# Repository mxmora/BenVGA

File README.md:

# BenVGA
Ben's VGA card in PCB form

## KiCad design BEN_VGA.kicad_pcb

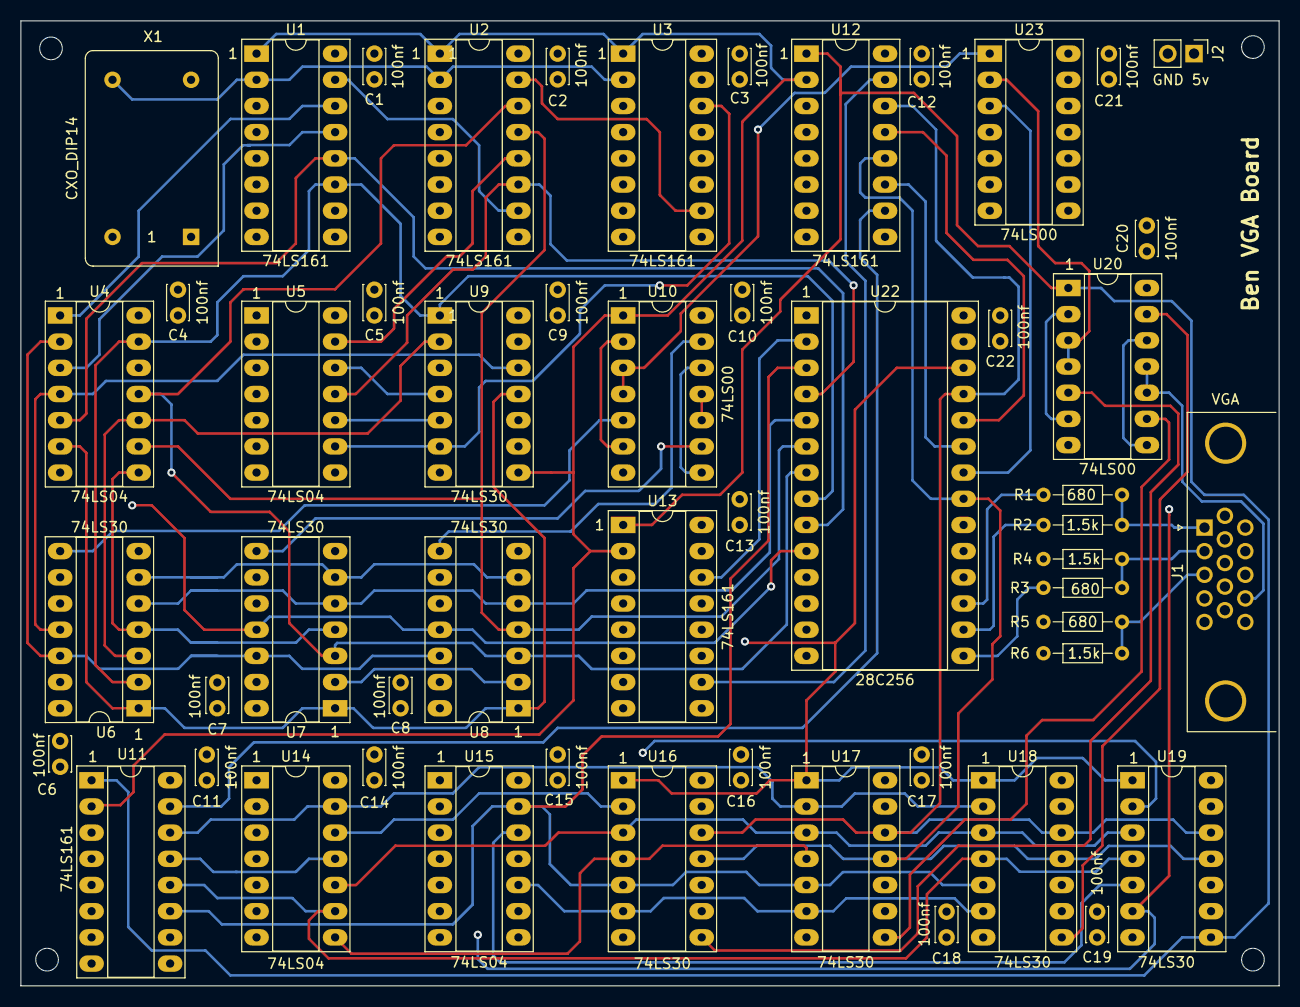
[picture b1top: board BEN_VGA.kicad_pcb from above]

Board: 4 copper layers, 122.0 x 93.6 mm, 57 parts (0 on the bottom side), 65 nets.

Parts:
C1, C2, C3, C4, C5, C6, C7, C8, C9, C10, C11, C12, C13, C14, C15, C16, C17, C18, C19, C20, C21, C22: 100nf; C_Disc_D3.4mm_W2.1mm_P2.50mm
H1, H2, H3, H4: MountingHole; MountingHole_2.2mm_M2
J1: VGA; DSUB-15-HD_Female_Horizontal_P2.29x1.98mm_EdgePinOffset3.03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
J2: GND 5v; PinHeader_1x02_P2.54mm_Vertical
R1, R3, R5: 680; R_Axial_DIN0204_L3.6mm_D1.6mm_P7.62mm_Horizontal
R2, R4, R6: 1.5k; R_Axial_DIN0204_L3.6mm_D1.6mm_P7.62mm_Horizontal
U1, U2, U3, U11, U12, U13: 74LS161; DIP-16_W7.62mm_Socket_LongPads
U4, U5, U14, U15: 74LS04; DIP-14_W7.62mm_Socket_LongPads
U6, U7, U8, U9, U16, U17, U18, U19: 74LS30; DIP-14_W7.62mm_Socket_LongPads
U10, U20, U23: 74LS00; DIP-14_W7.62mm_Socket_LongPads
U22: 28C256; DIP-28_W15.24mm_Socket_LongPads
X1: CXO_DIP14; Oscillator_DIP-14

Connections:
+5V: C1.1, C2.1, C3.1, C4.1, C5.1, C6.1, C7.1, C8.1, C9.1, C10.1, C11.1, C12.1, C13.1, C14.1, C15.1, C16.1, C17.1, C18.1, C19.1, C20.1, C21.1, C22.1, J2.1, U1.7, U1.9, U1.10, U1.16, U2.7, U2.9, U2.16, U3.7, U3.9, U3.16, U4.14, U5.14, U6.14, U7.14, U8.14, U9.14, U10.14, U11.7, U11.9, U11.10, U11.16, U12.7, U12.9, U12.16, U13.7, U13.9, U13.16, U14.14, U15.14, U16.14, U17.14, U18.7, U19.7, U20.14, U22.27, U22.28, U23.14, X1.1, X1.14
/HSync/264: U1.1, U2.1, U3.1, U9.8, U10.1, U11.2, U12.2, U13.2
/HSync/CLK: U1.2, U2.2, U3.2, X1.8
/HSync/HBLANK: U10.3, U10.4, U23.1
/HSync/Q0: U1.14, U4.1
/HSync/Q1: U1.13, U4.3, U7.11, U8.11, U22.10
/HSync/Q2: U1.12, U4.5, U22.9
/HSync/Q3: U1.11, U4.13, U6.2, U9.1, U22.8
/HSync/Q4: U2.14, U4.11, U7.3, U8.3, U22.7
/HSync/Q5: U2.13, U4.9, U8.4, U22.6
/HSync/Q6: U2.12, U5.13, U6.5, U7.5, U8.5, U22.5
/HSync/Q7: U2.11, U5.11, U6.6, U7.6, U8.6, U22.4
/HSync/Q8: U3.14, U5.9, U9.6
/VSync/Q0: U11.14, U14.13, U17.2, U18.2
/VSync/Q1: U11.13, U14.11
/VSync/Q2: U11.12, U14.9, U18.4, U19.4
/VSync/Q3: U11.11, U15.13, U16.5, U17.5, U18.5, U22.3
/VSync/Q4: U12.14, U16.12, U17.12, U18.12, U19.12, U22.25
/VSync/Q5: U12.13, U15.11, U19.6, U22.24
/VSync/Q6: U12.12, U16.11, U17.11, U18.11, U19.11, U22.21
/VSync/Q7: U12.11, U22.23
/VSync/Q8: U13.14, U22.2
/VSync/Q9: U13.13, U16.1, U17.1, U18.1, U19.1, U22.26
/VSync/VBLANK: U20.3, U20.4, U23.2
GND: C1.2, C2.2, C3.2, C4.2, C5.2, C6.2, C7.2, C8.2, C9.2, C10.2, C11.2, C12.2, C13.2, C14.2, C15.2, C16.2, C17.2, C18.2, C19.2, C20.2, C21.2, C22.2, J1.5, J1.6, J1.7, J1.8, J1.10, J2.2, U1.8, U2.8, U3.8, U4.7, U5.7, U6.7, U7.7, U8.7, U9.7, U10.7, U11.8, U12.8, U13.8, U14.7, U15.7, U16.7, U17.7, U18.14, U19.14, U20.7, U22.1, U22.14, U22.20, U23.7, X1.7
HSYNC: J1.13, U10.10, U10.11
unnamed: J1.1, R1.2, R2.2
unnamed: J1.2, R3.2, R4.2
unnamed: J1.3, R5.2, R6.2
unnamed: R1.1, U22.17
unnamed: R2.1, U22.16
unnamed: R3.1, U22.15
unnamed: R4.1, U22.13
unnamed: R5.1, U22.12
unnamed: R6.1, U22.11
unnamed: U1.15, U2.10
unnamed: U2.15, U3.10
unnamed: U4.2, U6.12, U7.12, U8.12
unnamed: U4.4, U6.11, U9.12
unnamed: U4.6, U6.1, U7.1, U8.1, U9.11
unnamed: U4.8, U6.4, U7.4, U9.3
unnamed: U4.10, U6.3, U9.2
unnamed: U4.12, U7.2, U8.2
unnamed: U5.10, U9.5
unnamed: U5.12, U9.4
unnamed: U10.2, U10.6
unnamed: U6.8, U10.5
unnamed: U7.8, U10.9
unnamed: U10.8, U10.12
unnamed: U8.8, U10.13
unnamed: U11.1, U12.1, U13.1, U19.8, U20.1
unnamed: U11.15, U12.10
unnamed: U12.15, U13.10
unnamed: U14.8, U16.4, U17.4
unnamed: U14.10, U16.3, U17.3, U18.3, U19.3
unnamed: U14.12, U16.2, U19.2
unnamed: U15.10, U16.6, U17.6, U18.6
unnamed: U15.12, U19.5
unnamed: U16.8, U20.5
unnamed: U17.8, U20.9
unnamed: U18.8, U20.13
unnamed: U20.2, U20.6
unnamed: U20.8, U20.12
unnamed: U22.22, U23.3
VSYNC: J1.14, U20.10, U20.11

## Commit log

2020-12-17 first check-in
2020-12-18 shrink the board
2020-12-18 small tweaks
